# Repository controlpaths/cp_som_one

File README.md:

# CP SOM ONE (kICAD -ALTIUM DESIGNER)

The CP SOM ONE is a Open Source System-On-Module that features an FPGA Artix7 from AMD. 

## KICAD Images

## ALTIUM Images

**More information in [controlpaths.com](https://www.controlpaths.com/2023/10/28/designing-a-fpga-som/)**

## Get yours

The CP SOM ONE is open source and all the files are shared. If you want to build your own, you can to go to the [JLCPCB](https://jlcpcb.com/?from=controlpaths) website, click on Order Now, and upload a zip file with all the fabrication files.

Then, you have to configure some aspects of the board. For this SOM, I just changed the Surface Finish to LeadFree HASL. Also, you can customize the color of your board.

When the PCB service options are ready, then you have to select the PCB Assembly process. here we have to set whether the components are on one or both sides of the board, and the quantity we need. 

Then, when we confirm the board, the web application will ask us for two files, the position file for the components, and the bill of materials. Both files are generated in KiCad and are available in the GitHub repository.

Finally, you have to complete the order and two weeks later, the board will be in your house.

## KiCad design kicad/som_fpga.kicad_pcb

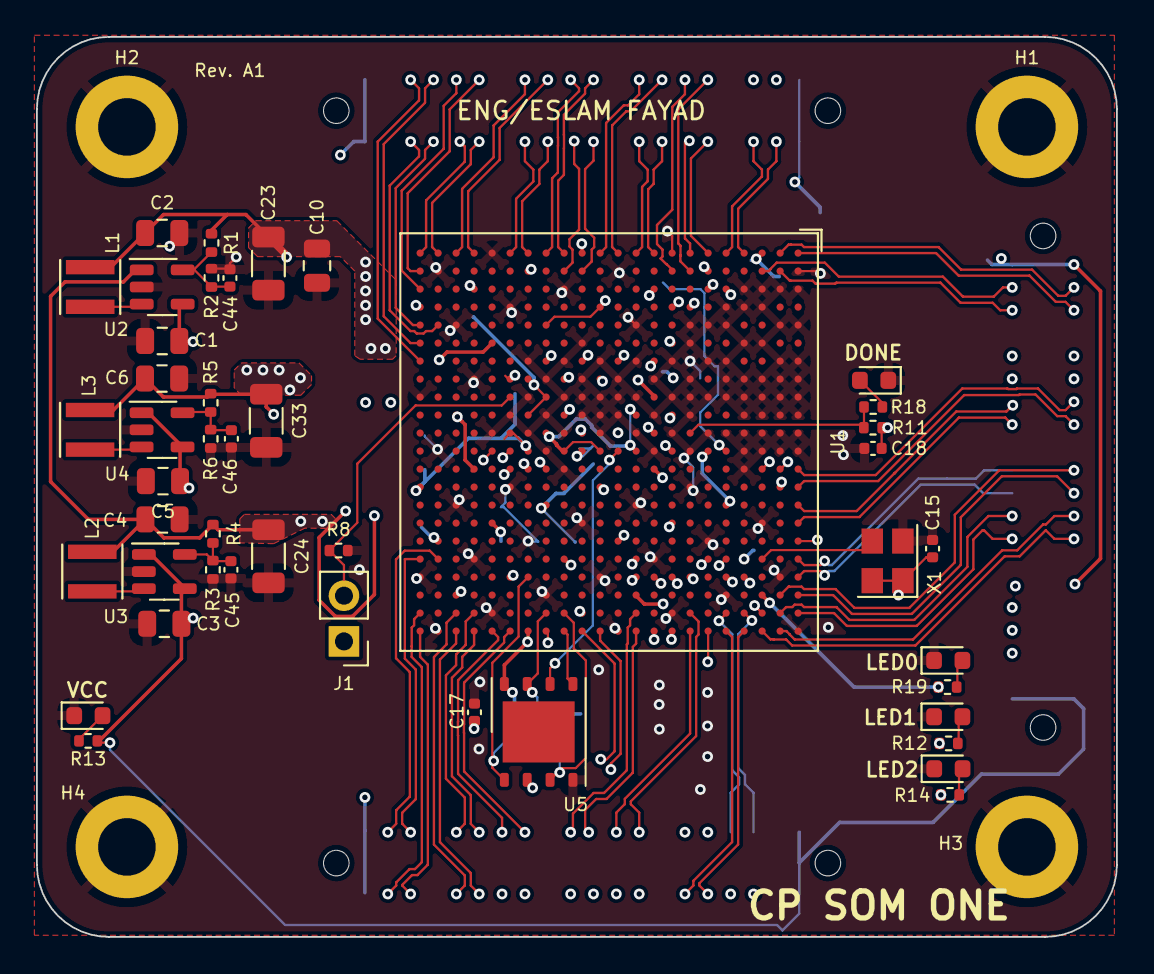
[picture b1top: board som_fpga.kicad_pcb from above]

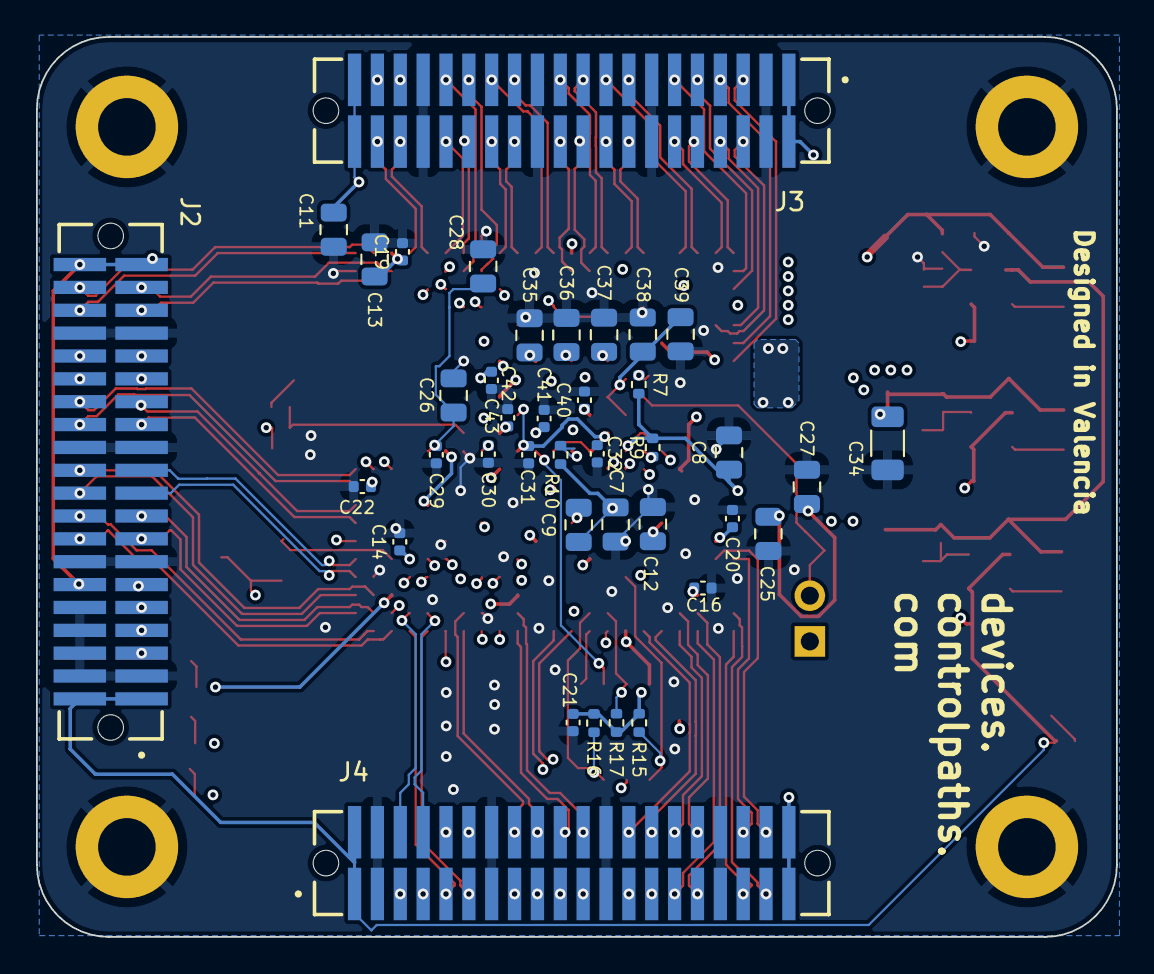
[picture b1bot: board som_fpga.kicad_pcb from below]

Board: 4 copper layers, 60.0 x 50.0 mm, 87 parts (39 on the bottom side), 111 nets.

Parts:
C1, C3, C5, C7, C8, C9, C10, C11, C12, C13, C25, C26, C27, C28, C35, C36, C37, C38, C39: 4u7; C_0805_2012Metric
C2, C4, C6: 10u; C_0805_2012Metric
C14, C15, C16, C17, C18, C19, C20, C21, C22, C29, C30, C31, C32, C40, C41, C42, C43, C44, C45, C46: 0.47u; C_0402_1005Metric
C23, C24: 47u; C_1206_3216Metric
C33, C34: 100u; C_1206_3216Metric
D1: DONE; LED_0603_1608Metric
D2: VCC; LED_0603_1608Metric
D3, D4, D5: USER_LED; LED_0603_1608Metric
H1, H2, H3, H4: MountingHole_Pad; MountingHole_3.2mm_M3_ISO7380_Pad
J1: Conn_01x02_Pin; PinHeader_1x02_P2.54mm_Vertical
J2, J3, J4: Conn_02x20_Odd_Even; SAMTEC_TFM-120-02-S-D-A
L1, L2, L3: 2u2; IND_LQH3NPN2R2MJRL
R1: 100k; R_0402_1005Metric
R2, R5: 22k; R_0402_1005Metric
R3: 120k; R_0402_1005Metric
R4: 240k; R_0402_1005Metric
R6: 33k; R_0402_1005Metric
R7, R8, R9, R10, R15, R16, R17: 4k7; R_0402_1005Metric
R11: 330; R_0402_1005Metric
R12, R13, R14, R19: 10k; R_0402_1005Metric
R18: 100; R_0402_1005Metric
U1: XC7A35T-FGG484; FB-BGA-484_23.0x23.0mm_Layout22x22_P1.0mm
U2, U3, U4: TLV62565DBVR; SOT-23-5
U5: MX25L12833F; WSON-8-1EP_6x5mm_P1.27mm_EP3.4x4mm
X1: SG-8018CE; Crystal_SMD_3225-4Pin_3.2x2.5mm

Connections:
+1V0: C6.1, C33.1, C34.1, C35.1, C36.1, C37.1, C38.1, C39.1, C40.1, C41.1, C42.1, C43.1, L3.2, R5.1, U1.H8 (VCCINT), U1.H10 (VCCINT), U1.J7 (VCCINT), U1.J9 (VCCINT), U1.J11 (VCCBRAM), U1.K8 (VCCINT), U1.L7 (VCCINT), U1.L11 (VCCBRAM), U1.M8 (VCCINT), U1.N7 (VCCINT), U1.N11 (VCCBRAM), U1.P8 (VCCINT), U1.P10 (VCCINT), U1.R7 (VCCINT), U1.R9 (VCCINT), U1.T8 (VCCINT), U1.T10 (VCCINT)
+1V8: C4.1, C24.1, C25.1, C26.1, C27.1, C28.1, C29.1, C30.1, C31.1, C32.1, L2.2, R4.1, U1.E12 (VCCBATT_0), U1.H12 (VCCAUX), U1.K10 (VCCADC_0), U1.K12 (VCCAUX), U1.M12 (VCCAUX), U1.P12 (VCCAUX), U1.R11 (VCCAUX), U2.1 (EN)
+3V3: C2.1, C7.1, C8.1, C9.1, C10.1, C11.1, C12.1, C13.1, C14.1, C15.1, C16.1, C17.1, C18.1, C19.1, C20.1, C21.1, C22.1, C23.1, J1.1, J2.12, J2.39, J2.40, J3.39, J3.40, J4.39, J4.40, L1.2, R1.1, R7.2, R9.2, R10.2, R11.2, R15.1, R16.1, R17.1, U1.A17 (VCCO_16), U1.AA7 (VCCO_34), U1.AA17 (VCCO_13), U1.AB4 (VCCO_34), U1.AB14 (VCCO_13), U1.B14 (VCCO_16), U1.C1 (VCCO_35), U1.C21 (VCCO_16), U1.D18 (VCCO_16), U1.E15 (VCCO_16), U1.F2 (VCCO_35), U1.F12 (VCCO_0), U1.F22 (VCCO_16), U1.G19 (VCCO_15), U1.H6 (VCCO_35), U1.H16 (VCCO_15), U1.J3 (VCCO_35), U1.J13 (VCCO_15), U1.K20 (VCCO_15), U1.L17 (VCCO_15), U1.M4 (VCCO_35), U1.M14 (VCCO_14), U1.N1 (VCCO_35), U1.N21 (VCCO_15), U1.P18 (VCCO_14), U1.R5 (VCCO_34), U1.R15 (VCCO_14), U1.T2 (VCCO_34), U1.T12 (VCCO_0), U1.T22 (VCCO_14), U1.U11 (M0_0), U1.U19 (VCCO_14), U1.V6 (VCCO_34), U1.V16 (VCCO_13), U1.W3 (VCCO_34), U1.W13 (VCCO_13), U1.Y10 (VCCO_13), U1.Y20 (VCCO_14), U5.8 (VCC), X1.1 (OE), X1.4 (Vcc)
+5V: C1.1, C3.1, C5.1, J2.1, J2.2, J3.1, J3.2, J4.1, J4.2, R13.1, U2.4 (VIN), U3.1 (EN), U3.4 (VIN), U4.1 (EN), U4.4 (VIN)
/FPGA_bank13_14/FLASH_CS: R15.2, U1.T19 (IO_L6P_T0_FCS_B_14), U5.1 (~CS)
/FPGA_bank13_14/FLASH_D0: U1.P22 (IO_L1P_T0_D00_MOSI_14), U5.5 (SI/SIO0)
/FPGA_bank13_14/FLASH_D1: U1.R22 (IO_L1N_T0_D01_DIN_14), U5.2 (SO/SIO1)
/FPGA_bank13_14/FLASH_D2: R16.2, U1.P21 (IO_L2P_T0_D02_14), U5.3 (~WP/SIO2)
/FPGA_bank13_14/FLASH_D3: R17.2, U1.R21 (IO_L2N_T0_D03_14), U5.7 (~RESET/SIO3)
CONN1.1_N: J3.7, U1.AB6 (IO_L20N_T3_34)
CONN1.1_P: J3.5, U1.AB7 (IO_L20P_T3_34)
CONN1.2_N: J3.8, U1.AB5 (IO_L10N_T1_34)
CONN1.2_P: J3.6, U1.AA5 (IO_L10P_T1_34)
CONN1.3_N: J3.11, U1.AB2 (IO_L8N_T1_34)
CONN1.3_P: J3.9, U1.AB3 (IO_L8P_T1_34)
CONN1.4_N: J3.10, U1.AB1 (IO_L7N_T1_34)
CONN1.4_P: J3.12, U1.AA1 (IO_L7P_T1_34)
CONN1.5_N: J3.15, U1.Y1 (IO_L5N_T0_34)
CONN1.5_P: J3.17, U1.W1 (IO_L5P_T0_34)
CONN1.6_N: J3.16, U1.U1 (IO_L1N_T0_34)
CONN1.6_P: J3.18, U1.T1 (IO_L1P_T0_34)
CONN1.7_N: J3.21, U1.P1 (IO_L20N_T3_35)
CONN1.7_P: J3.19, U1.R1 (IO_L20P_T3_35)
CONN1.8_N: J3.22, U1.N2 (IO_L22N_T3_35)
CONN1.8_P: J3.20, U1.P2 (IO_L22P_T3_35)
CONN1.9_N: J3.27, U1.L1 (IO_L15N_T2_DQS_35)
CONN1.9_P: J3.25, U1.M1 (IO_L15P_T2_DQS_35)
CONN1.10_N: J3.28, U1.J1 (IO_L7N_T1_AD6N_35)
CONN1.10_P: J3.26, U1.K1 (IO_L7P_T1_AD6P_35)
CONN1.11_N: J3.31, U1.G2 (IO_L8N_T1_AD14N_35)
CONN1.11_P: J3.29, U1.H2 (IO_L8P_T1_AD14P_35)
CONN1.12_N: J3.32, U1.F1 (IO_L5N_T0_AD13N_35)
CONN1.12_P: J3.30, U1.G1 (IO_L5P_T0_AD13P_35)
CONN1.13_N: J3.37, U1.G4 (IO_L12N_T1_MRCC_35)
CONN1.13_P: J3.35, U1.H4 (IO_L12P_T1_MRCC_35)
CONN1.14_N: J3.38, U1.D1 (IO_L3N_T0_DQS_AD5N_35)
CONN1.14_P: J3.36, U1.E1 (IO_L3P_T0_DQS_AD5P_35)
CONN2.1_N: J4.5, U1.D19 (IO_L14N_T2_SRCC_16)
CONN2.1_P: J4.7, U1.E19 (IO_L14P_T2_SRCC_16)
CONN2.2_N: J4.6, U1.D21 (IO_L23N_T3_16)
CONN2.2_P: J4.8, U1.E21 (IO_L23P_T3_16)
CONN2.3_N: J4.9, U1.D22 (IO_L22N_T3_16)
CONN2.3_P: J4.11, U1.E22 (IO_L22P_T3_16)
CONN2.4_N: J4.10, U1.E18 (IO_L15N_T2_DQS_16)
CONN2.4_P: J4.12, U1.F18 (IO_L15P_T2_DQS_16)
CONN2.5_N: J4.15, U1.H19 (IO_L12N_T1_MRCC_15)
CONN2.5_P: J4.17, U1.J19 (IO_L12P_T1_MRCC_15)
CONN2.6_N: J4.18, U1.G22 (IO_L24N_T3_16)
CONN2.6_P: J4.16, U1.G21 (IO_L24P_T3_16)
CONN2.7_N: J4.21, U1.K19 (IO_L13N_T2_MRCC_15)
CONN2.7_P: J4.19, U1.K18 (IO_L13P_T2_MRCC_15)
CONN2.8_N: J4.20, U1.K22 (IO_L9N_T1_DQS_AD3N_15)
CONN2.8_P: J4.22, U1.K21 (IO_L9P_T1_DQS_AD3P_15)
CONN2.9_N: J4.25, U1.M22 (IO_L15N_T2_DQS_ADV_B_15)
CONN2.9_P: J4.27, U1.N22 (IO_L15P_T2_DQS_15)
CONN2.10_N: J4.28, U1.V22 (IO_L3N_T0_DQS_EMCCLK_14)
CONN2.10_P: J4.26, U1.U22 (IO_L3P_T0_DQS_PUDC_B_14)
CONN2.11_N: J4.29, U1.Y22 (IO_L9N_T1_DQS_D13_14)
CONN2.11_P: J4.31, U1.Y21 (IO_L9P_T1_DQS_14)
CONN2.12_N: J4.30, U1.W22 (IO_L7N_T1_D10_14)
CONN2.12_P: J4.32, U1.W21 (IO_L7P_T1_D09_14)
CONN2.13_N: J4.35, U1.AB22 (IO_L10N_T1_D15_14)
CONN2.13_P: J4.37, U1.AB21 (IO_L10P_T1_D14_14)
CONN2.14_N: J4.36, U1.AB18 (IO_L17N_T2_A13_D29_14)
CONN2.14_P: J4.38, U1.AA18 (IO_L17P_T2_A14_D30_14)
CONN3.5_N: J2.15, U1.A21 (IO_L21N_T3_DQS_16)
CONN3.5_P: J2.17, U1.B21 (IO_L21P_T3_DQS_16)
CONN3.6_N: J2.18, U1.B22 (IO_L20N_T3_16)
CONN3.6_P: J2.16, U1.C22 (IO_L20P_T3_16)
CONN3.7_N: J2.19, U1.A19 (IO_L17N_T2_16)
CONN3.7_P: J2.21, U1.A18 (IO_L17P_T2_16)
CONN3.8_N: J2.20, U1.A20 (IO_L16N_T2_16)
CONN3.8_P: J2.22, U1.B20 (IO_L16P_T2_16)
CONN3.9_N: J2.25, U1.A16 (IO_L9N_T1_DQS_16)
CONN3.9_P: J2.27, U1.A15 (IO_L9P_T1_DQS_16)
CONN3.10_N: J2.26, U1.A14 (IO_L10N_T1_16)
CONN3.10_P: J2.28, U1.A13 (IO_L10P_T1_16)
CONN3.11_N: J2.29, U1.B13 (IO_L8N_T1_16)
CONN3.11_P: J2.31, U1.C13 (IO_L8P_T1_16)
CONN3.12_N: J2.30, U1.E3 (IO_L6N_T0_VREF_35)
CONN3.12_P: J2.32, U1.F3 (IO_L6P_T0_35)
CONN3.13_N: J2.35, U1.B2 (IO_L2N_T0_AD12N_35)
CONN3.13_P: J2.37, U1.C2 (IO_L2P_T0_AD12P_35)
CONN3.14_N: J2.36, U1.A1 (IO_L1N_T0_AD4N_35)
CONN3.14_P: J2.38, U1.B1 (IO_L1P_T0_AD4P_35)
FLASH_SCLK: U1.L12 (CCLK_0), U5.6 (SCLK)
GND: C1.2, C2.2, C3.2, C4.2, C5.2, C6.2, C7.2, C8.2, C9.2, C10.2, C11.2, C12.2, C13.2, C14.2, C15.2, C16.2, C17.2, C18.2, C19.2, C20.2, C21.2, C22.2, C23.2, C24.2, C25.2, C26.2, C27.2, C28.2, C29.2, C30.2, C31.2, C32.2, C33.2, C34.2, C35.2, C36.2, C37.2, C38.2, C39.2, C40.2, C41.2, C42.2, C43.2, C44.2, C45.2, C46.2, D1.1 (K), D2.1 (K), D3.1 (K), D4.1 (K), D5.1 (K), H1.1, H2.1, H3.1, H4.1, J2.3, J2.4, J2.6, J2.8, J2.10, J2.13, J2.14, J2.23, J2.24, J2.33, J2.34, J3.3, J3.4, J3.13, J3.14, J3.23, J3.24, J3.33, J3.34, J4.3, J4.4, J4.13, J4.14, J4.23, J4.24, J4.33, J4.34, R2.2, R3.2, R6.2, R8.2, U1.A2 (GND), U1.A3 (GND), U1.A5 (GND), U1.A7 (GND), U1.A8 (MGTPRXN0_216), U1.A9 (GND), U1.A10 (MGTPRXN2_216), U1.A11 (GND), U1.A12 (GND), U1.A22 (GND), U1.AA2 (GND), U1.AA12 (GND), U1.AA22 (GND), U1.AB9 (GND), U1.AB19 (GND), U1.B3 (GND), U1.B5 (MGTAVTT), U1.B7 (MGTAVTT), U1.B8 (MGTPRXP0_216), U1.B9 (MGTAVTT), U1.B10 (MGTPRXP2_216), U1.B11 (MGTAVTT), U1.B12 (GND), U1.B19 (GND), U1.C3 (GND), U1.C4 (MGTAVTT), U1.C6 (GND), U1.C8 (MGTAVTT), U1.C9 (MGTPRXN3_216), U1.C10 (GND), U1.C11 (MGTPRXN1_216), U1.C12 (GND), U1.C16 (GND), U1.D3 (GND), U1.D4 (GND), U1.D6 (MGTAVCC), U1.D8 (GND), U1.D9 (MGTPRXP3_216), U1.D10 (MGTAVCC), U1.D11 (MGTPRXP1_216), U1.D12 (GND), U1.D13 (GND), U1.E4 (GND), U1.E5 (GND), U1.E7 (GND), U1.E8 (MGTAVCC), U1.E9 (GND), U1.E11 (GND), U1.E20 (GND), U1.F5 (GND), U1.F7 (MGTAVCC), U1.F9 (MGTAVCC), U1.F11 (GND), U1.F17 (GND), U1.G5 (GND), U1.G6 (GND), U1.G7 (GND), U1.G8 (GND), U1.G9 (GND), U1.G10 (GND), U1.G12 (GND), U1.G14 (GND), U1.H1 (GND), U1.H7 (GND), U1.H9 (GND), U1.H11 (GND), U1.H21 (GND), U1.J8 (GND), U1.J10 (GND), U1.J12 (GND), U1.J18 (GND), U1.K5 (GND), U1.K7 (GND), U1.K9 (GNDADC_0), U1.K11 (GND), U1.K15 (GND), U1.L2 (GND), U1.L8 (GND), U1.L9 (VREFN_0), U1.L10 (VP_0), U1.L22 (GND), U1.M7 (GND), U1.M9 (VN_0), U1.M10 (VREFP_0), U1.M11 (GND), U1.M19 (GND), U1.N6 (GND), U1.N8 (GND), U1.N9 (DXN_0), U1.N10 (DXP_0), U1.N16 (GND), U1.P3 (GND), U1.P7 (GND), U1.P9 (GND), U1.P11 (GND), U1.P13 (GND), U1.R8 (GND), U1.R10 (GND), U1.R12 (GND), U1.R20 (GND), U1.T7 (GND), U1.T9 (GND), U1.T11 (GND), U1.T17 (GND), U1.U4 (GND), U1.U10 (M1_0), U1.U14 (GND), U1.V1 (GND), U1.V11 (GND), U1.V21 (GND), U1.W8 (GND), U1.W18 (GND), U1.Y5 (GND), U1.Y15 (GND), U2.2 (GND), U3.2 (GND), U4.2 (GND), U5.4 (GND), X1.2 (GND)
JTAG_TCK: J2.7, U1.V12 (TCK_0)
JTAG_TDI: J2.11, U1.R13 (TDI_0)
JTAG_TDO: J2.9, U1.U13 (TDO_0)
JTAG_TMS: J2.5, U1.T13 (TMS_0)
unnamed: D1.2 (A), R18.1
unnamed: D2.2 (A), R13.2
unnamed: D3.2 (A), R12.2
unnamed: D4.2 (A), R14.2
unnamed: D5.2 (A), R19.2
unnamed: J1.2, R8.1, U1.U9 (M2_0)
unnamed: U1.C18 (IO_L13P_T2_MRCC_16), X1.3 (OUT)
unnamed: R7.1, U1.U8 (CFGBVS_0)
unnamed: R11.1, R18.2, U1.G11 (DONE_0)
unnamed: R9.1, U1.U12 (INIT_B_0)
unnamed: R10.1, U1.N12 (PROGRAM_B_0)
unnamed: C44.1, R1.2, R2.1, U2.5 (FB)
unnamed: L1.1, U2.3 (SW)
unnamed: C45.1, R3.1, R4.2, U3.5 (FB)
unnamed: L2.1, U3.3 (SW)
unnamed: C46.1, R5.2, R6.1, U4.5 (FB)
unnamed: L3.1, U4.3 (SW)
USER_LED0: R19.1, U1.C20 (IO_L19N_T3_VREF_16)
USER_LED1: R12.1, U1.H22 (IO_L7N_T1_AD2N_15)
USER_LED2: R14.1, U1.J22 (IO_L7P_T1_AD2P_15)

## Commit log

2023-10-29 First version
2023-10-30 readme updated
2023-11-02 Supply fb resistor marked as Not Populated
2024-09-09 Create LICENSE
2025-10-12 cp_som_Altium imported
2025-10-12 folder arrangment
2025-10-12 ADD_ALTIUM IMAGES
